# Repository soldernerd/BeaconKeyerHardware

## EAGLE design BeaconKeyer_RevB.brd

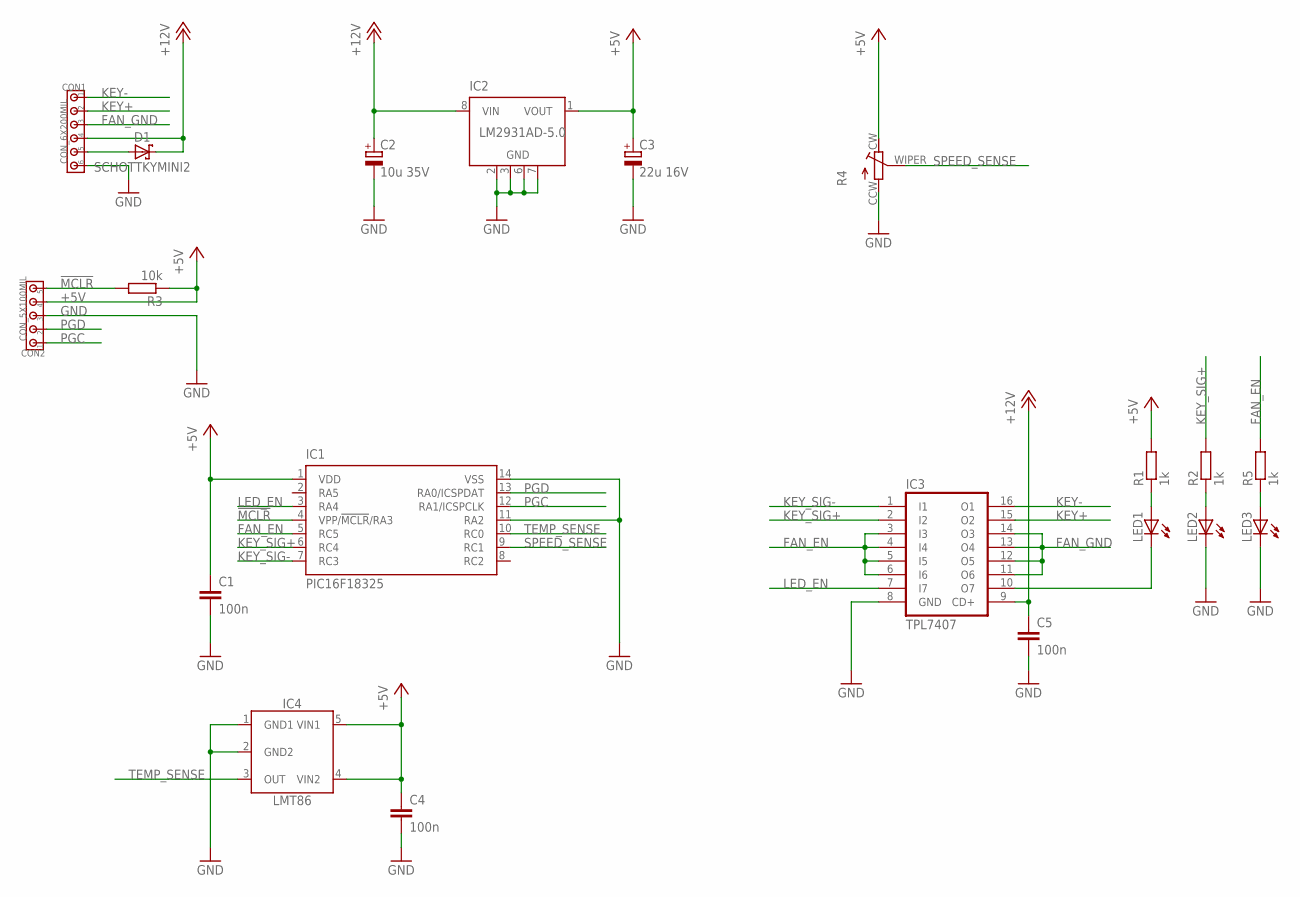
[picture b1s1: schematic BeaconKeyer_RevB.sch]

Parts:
C1, C4, C5: 100n; C0805
C2: 10u 35V; SMC_C
C3: 22u 16V; SMC_C
CON1: CON_6X200MIL; 200MIL_6X
CON2: CON_5X100MIL; 100MIL_5X
D1: SCHOTTKYMINI2; MINI2-F3-B
IC1: PIC16F18325; SO14
IC2: LM2931AD-5.0; SOIC8
IC3: TPL7407; SO16
IC4: LMT86; SC70-5
LED1, LED2, LED3: LED0805
R1, R2, R5: 1k; R0805
R3: 10k; R0805
R4: TRIMMER3314G; RTRIM3314G

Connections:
!MCLR!: CON2.5, IC1.4 (VPP/!MCLR!/RA3), R3.2
+5V: C1.1, C3.+, C4.1, CON2.4, IC1.1 (VDD), IC2.1 (VOUT), IC4.4 (VIN2), IC4.5 (VIN1), R1.2, R3.1, R4.CW
+12V: C2.+, C5.1, CON1.4, D1.C, IC2.8 (VIN), IC3.9 (CD+)
FAN_EN: IC1.5 (RC5), IC3.3 (I3), IC3.4 (I4), IC3.5 (I5), IC3.6 (I6), R5.2
FAN_GND: CON1.3, IC3.11 (O6), IC3.12 (O5), IC3.13 (O4), IC3.14 (O3)
GND: C1.2, C2.-, C3.-, C4.2, C5.2, CON1.6, CON2.3, IC1.11 (RA2), IC1.14 (VSS), IC2.2 (GND), IC2.3 (GND), IC2.6 (GND), IC2.7 (GND), IC3.8 (GND), IC4.1 (GND1), IC4.2 (GND2), LED2.C, LED3.C, R4.CCW
KEY+: CON1.2, IC3.15 (O2)
KEY-: CON1.1, IC3.16 (O1)
KEY_SIG+: IC1.6 (RC4), IC3.2 (I2), R2.2
KEY_SIG-: IC1.7 (RC3), IC3.1 (I1)
LED_EN: IC1.3 (RA4), IC3.7 (I7)
unnamed: LED2.A, R2.1
unnamed: LED1.A, R1.1
unnamed: IC3.10 (O7), LED1.C
unnamed: LED3.A, R5.1
PGC: CON2.1, IC1.12 (RA1/ICSPCLK)
PGD: CON2.2, IC1.13 (RA0/ICSPDAT)
SPEED_SENSE: IC1.9 (RC1), R4.WIPER
TEMP_SENSE: IC1.10 (RC0), IC4.3 (OUT)
VIN: CON1.5, D1.A

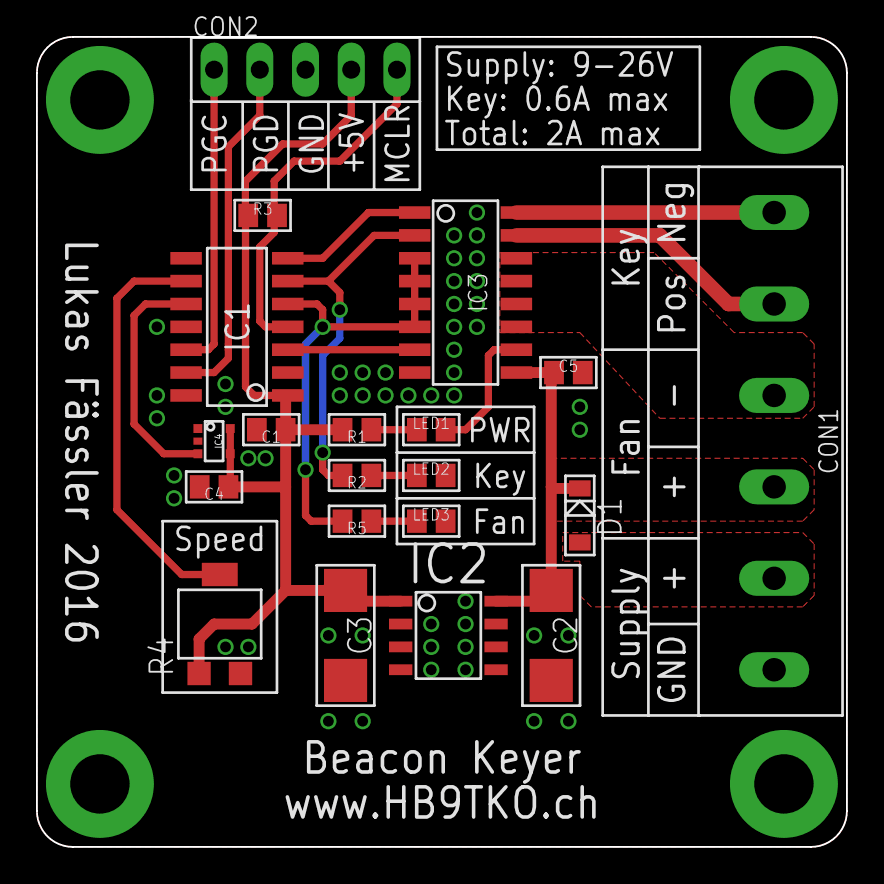
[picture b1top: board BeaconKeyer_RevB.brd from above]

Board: 2 copper layers, 45.0 x 45.0 mm, 20 parts (0 on the bottom side), 20 nets.

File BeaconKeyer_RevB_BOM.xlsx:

Quantity | Description | Value | Package | Manufacturer | Model | Marking | Farnell | Remarks | Parts | Unit Price | Price | Price inkl MwSt
1 | PCB |  | 45x45mm | Soldernerd.com |  |  |  |  | n/a | 3 | 3 | 3
1 | 5-Pin Header | n/a | 100 mil (2.54mm) | TE Connectivity / AMP | 826926-5 | n/a | 1248143 | or similar | CON2 | 0.153 | 0.153 | 0.16630434782608694
1 | 6-Pin Header | n/a | 200 mil (3.08mm) | Weidmueller |  | n/a |  | or similar | CON1 | 0.6 | 0.6 | 0.65217391304347816
1 | Tantal capacitor | 10uF, 35V | Case C | KEMET | T491C106K035AT | 106 35K | 1457464 |  | C2 | 0.8 | 0.8 | 0.86956521739130432
1 | Tantal capacitor | 33uF, 16V | Case C |  |  |  |  |  | C3 | 0.8 | 0.8 | 0.86956521739130432
3 | Ceramic capacitor | 100nF, 50V, X7R | 75x65mm | Multicomp | MC0805B104K500CT | n/a | 1759265 | or similar | C1, C4, C5 | 1.46E-2 | 4.3799999999999999E-2 | 4.7608695652173912E-2
1 | 7-channel low-side driver | n/a | SOIC16 | Texas Instruments | TPL7407 | TPL7407 | 2400932 |  | IC3 | 0.56000000000000005 | 0.56000000000000005 | 0.60869565217391308
3 | Resistor | 1kOhms | 0805, metric 2012 | Multicomp | MC01W080511K | 1001 | 9332383 | or similar | R1, R2, R5 | 2.2000000000000001E-3 | 6.6E-3 | 7.1739130434782606E-3
1 | Resistor | 10kOhms | 0805, metric 2012 | Multicomp | MC01W0805110K | 1002 | 9332391 | or similar | R3 | 1.8E-3 | 1.8E-3 | 1.9565217391304345E-3
1 | Trimmer | 5k or 10k | RTRIM | Bourns | 3314G-2-103E |  | 2328476 |  | R4 | 1.41 | 1.41 | 1.5326086956521738
1 | Analog Temperature Sensors with Class-AB Output | LMT86 | SC70-5 | Texas Instruments | LMT86 |  | 2314388 |  | IC4 | 0.55000000000000004 | 0.55000000000000004 | 0.59782608695652173
1 | LED | green | 0805, metric 2012 | Multicomp | OVS-0804 | n/a | 1716766 | or similar | LED1 | 0.28999999999999998 | 0.28999999999999998 | 0.31521739130434778
2 | LED | red | 0805, metric 2012 | Knightbridge | KP-2012SECK-J3 | n/a | 2335811 | or similar | LED2, LED3 | 0.24 | 0.48 | 0.52173913043478259
1 | Schottky Diode | 60V 2A | MINI2-F3-B | Panasonic | DB2W60400L | n/a | 2284958 | or similar | D1 | 0.16 | 0.16 | 0.17391304347826086
1 | Linear Voltage Regulator | 5V | SOIC8 | Texas Instruments | LM2931AD-5.0 | LM2931 | 2534193 |  | IC2 | 0.55000000000000004 | 0.55000000000000004 | 0.59782608695652173
1 | 8-bit Microcontroller | n/a | SOIC14 | Microchip | PIC16F18325-I/SL | PIC16F18325 | 2474832 |  | IC1 | 1 | 1 | 1.0869565217391304
 |  |  |  |  |  |  |  |  |  |  |  | 11.04913043478261

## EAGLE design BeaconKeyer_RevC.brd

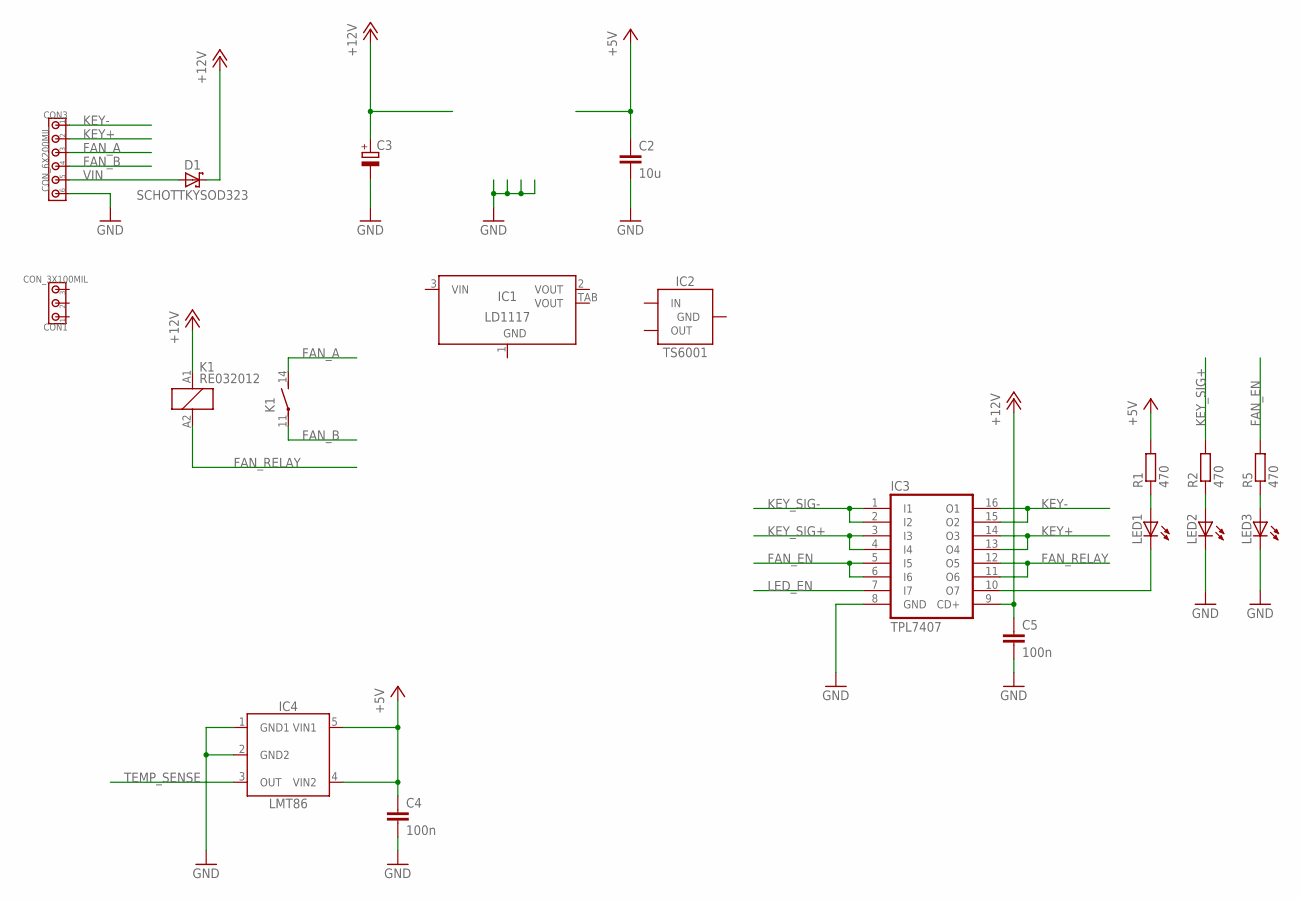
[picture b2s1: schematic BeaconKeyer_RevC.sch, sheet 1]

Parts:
C2: 10u; C0805
C3: C_POLARIZEDSMC_B; SMC_B
C4, C5: 100n; C0805
CON1: CON_3X100MIL; 100MIL_3X
CON3: CON_6X200MIL; 200MIL_6X
D1: SCHOTTKYSOD323; SOD323
IC1: LD1117; SOT223
IC2: TS6001; SOT23
IC3: TPL7407; SO16
IC4: LMT86; SC70-5
K1: RE032012; RE-SCHRACK
LED1, LED2, LED3: LED0805
R1, R2, R5: 470; R0805

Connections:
+5V: C2.1, C4.1, IC4.4 (VIN2), IC4.5 (VIN1), R1.2
+12V: C3.+, C5.1, D1.C, IC3.9 (CD+), K1.A1 (1); also elsewhere on the board
FAN_A: CON3.3, K1.14 (S)
FAN_B: CON3.4, K1.11
FAN_EN: IC3.5 (I5), IC3.6 (I6), R5.2
FAN_RELAY: IC3.11 (O6), IC3.12 (O5), K1.A2 (2)
GND: C2.2, C3.-, C4.2, C5.2, CON3.6, IC1.1 (GND), IC2.3 (GND), IC3.8 (GND), IC4.1 (GND1), IC4.2 (GND2), LED2.C, LED3.C; also elsewhere on the board
IN: IC2.1 (IN)
KEY+: CON3.2, IC3.13 (O4), IC3.14 (O3)
KEY-: CON3.1, IC3.15 (O2), IC3.16 (O1)
KEY_SIG+: IC3.3 (I3), IC3.4 (I4), R2.2
KEY_SIG-: IC3.1 (I1), IC3.2 (I2)
LED_EN: IC3.7 (I7)
unnamed: LED2.A, R2.1
unnamed: LED1.A, R1.1
unnamed: IC3.10 (O7), LED1.C
unnamed: LED3.A, R5.1
TEMP_SENSE: IC4.3 (OUT)
VIN: CON3.5, D1.A

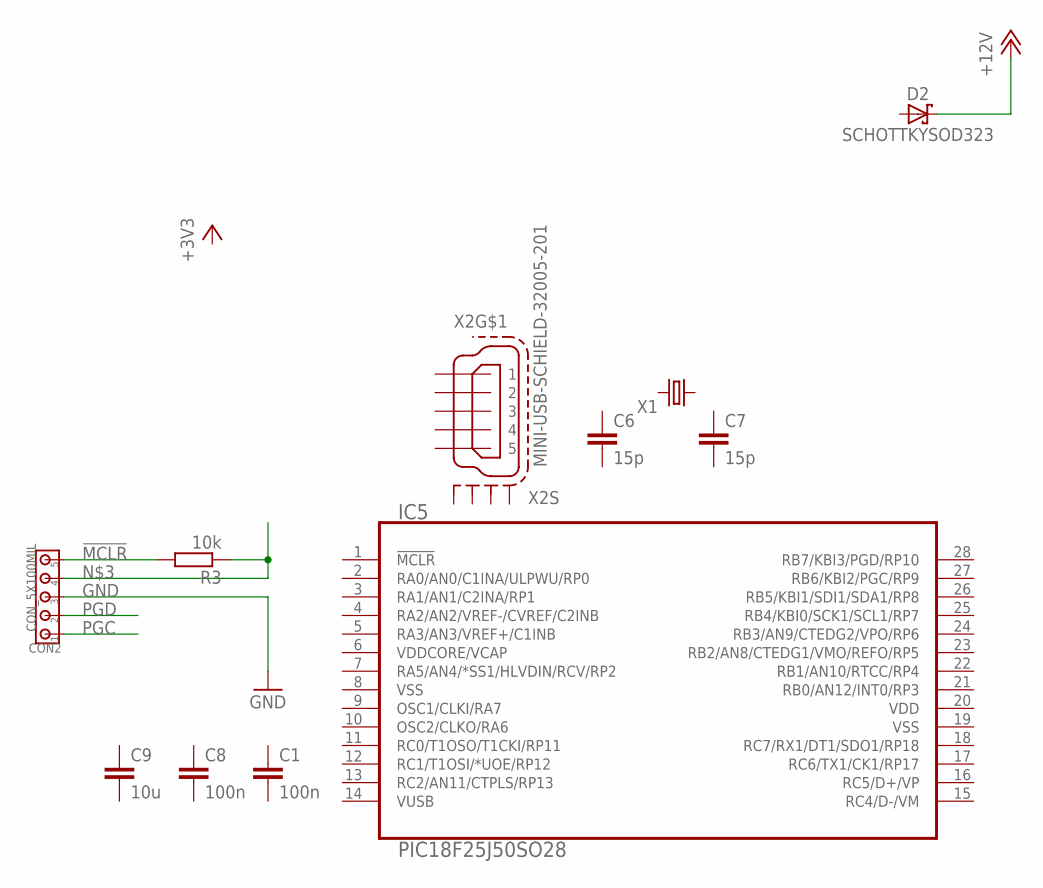
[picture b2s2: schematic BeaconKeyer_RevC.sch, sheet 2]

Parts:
C1, C8: 100n; C0805
C6, C7: 15p; C0805
C9: 10u; C0805
CON2: CON_5X100MIL; 100MIL_5X
D2: SCHOTTKYSOD323; SOD323
IC5: PIC18F25J50SO28; SO28W
R3: 10k; R0805
X1: CRYSTAL5X3.2MM; 5X3.2MM
X2: MINI-USB-SCHIELD-32005-201; 32005-201

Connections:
!MCLR!: CON2.5, R3.2
+12V: D2.C; also elsewhere on the board
GND: CON2.3; also elsewhere on the board
unnamed: CON2.4, R3.1
PGC: CON2.1
PGD: CON2.2
VDD: IC5.20 (VDD)
VDDCORE/VCAP: IC5.6 (VDDCORE/VCAP)
VUSB: IC5.14 (VUSB)

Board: 2 copper layers, 29 parts (0 on the bottom side), 18 nets, no tracks yet.

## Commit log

2024-11-01 Adding last version of RevB
